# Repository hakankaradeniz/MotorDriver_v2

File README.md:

# MotorDriver_v2
MotorDriver_v2

Hello my name is Hakan Karadeniz.

This board was designed by me in my internship in Portugal/Coimbra University in Computer and Electronics Engineering Department in Embedded Systems Lab.

You can read the DRV8231A data sheet for use.

You can run it with AutoDesk Eagle and Fusion360 programs.

Thank you.
Hakan
31.03.2023

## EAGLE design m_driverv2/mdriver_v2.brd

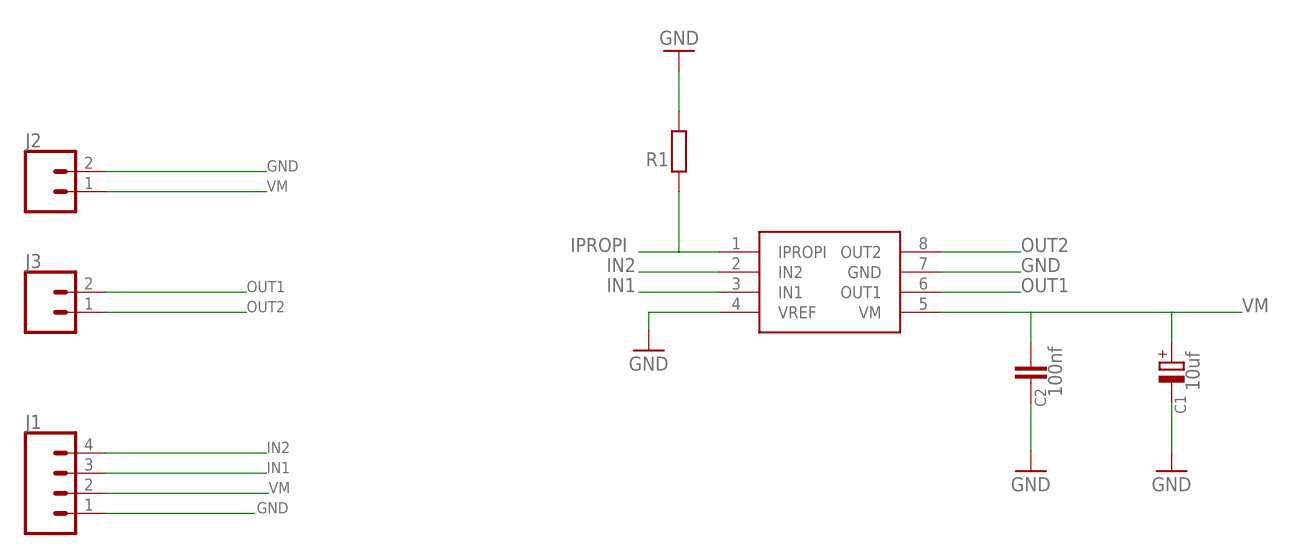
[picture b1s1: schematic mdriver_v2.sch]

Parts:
C1: 10uf; E2,5-6E
C2: 100nf; C025-025X050
J1: CONN_04; 1X04
J2, J3: CONN_02; 1X02
R1: SMK
U$1: DRV8231A; SOIC127P580X170-9T271X340N

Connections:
GND: C1.-, C2.2, J1.1, J2.2, R1.1, U$1.4 (VREF), U$1.7 (GND)
IN1: J1.3, U$1.3 (IN1)
IN2: J1.4, U$1.2 (IN2)
IPROPI: R1.2, U$1.1 (IPROPI)
OUT1: J3.2, U$1.6 (OUT1)
OUT2: J3.1, U$1.8 (OUT2)
VM: C1.+, C2.1, J1.2, J2.1, U$1.5 (VM)

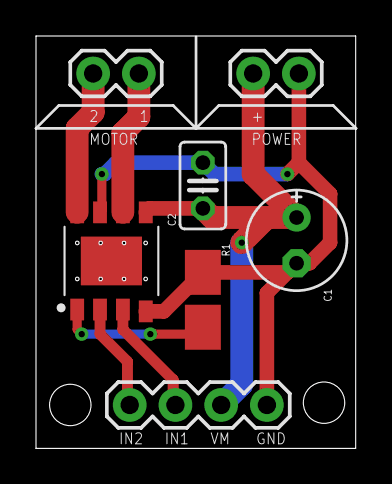
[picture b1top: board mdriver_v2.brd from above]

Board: 2 copper layers, 17.8 x 22.9 mm, 7 parts (0 on the bottom side), 7 nets.

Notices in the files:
parts and their libraries:
SparkFun-Connectors: Licensing: Creative Commons ShareAlike 4.0 International - https://creativecommons.org/licenses/by-sa/4.0
